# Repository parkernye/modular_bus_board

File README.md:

# modular_bus_board
Modular Synth Bus Board

A PCB that distributes the 10pin or 16pin standard modular synth power. 
LED's for power indication

Future Modifications: 
- Thicker board, or board stiffener

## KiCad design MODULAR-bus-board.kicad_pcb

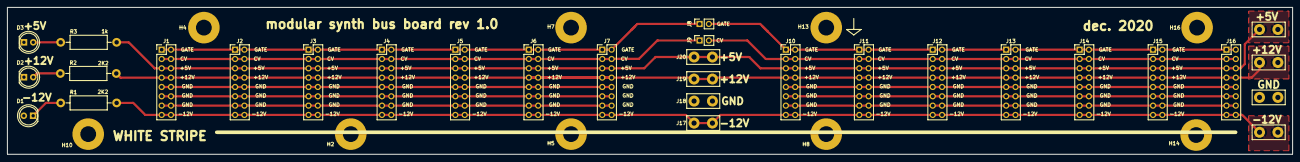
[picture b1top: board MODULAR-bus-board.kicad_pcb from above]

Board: 2 copper layers, 350.0 x 40.0 mm, 39 parts (0 on the bottom side), 11 nets.

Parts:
D1, D2: RED; LED_D5.0mm
D3: YELLOW; LED_D5.0mm
H2, H4, H5, H7, H8, H10, H13, H14, H16: MountingHole_Pad; MountingHole_4.3mm_M4_Pad
J1, J2, J3, J4, J5, J6, J7, J10, J11, J12, J13, J14, J15, J16: Conn_02x08_Odd_Even; PinHeader_2x08_P2.54mm_Vertical
J8, J9: Conn_01x02; PinSocket_1x02_P2.54mm_Vertical
J17, J18, J19, J20, J21: -12V; PCB WELDING TERMINAL TAB PC250
J22: GND; PCB WELDING TERMINAL TAB PC250
J23: +12V; PCB WELDING TERMINAL TAB PC250
J24: +5V; PCB WELDING TERMINAL TAB PC250
R1, R2: 2K2; R_Axial_DIN0411_L9.9mm_D3.6mm_P15.24mm_Horizontal
R3: 1K; R_Axial_DIN0411_L9.9mm_D3.6mm_P15.24mm_Horizontal

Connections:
GND: D1.2, D2.1, D3.1, H2.1, H4.1, H5.1, H7.1, H8.1, H10.1, H13.1, H14.1, H16.1, J1.9, J1.10, J1.11, J1.12, J1.13, J1.14, J2.9, J2.10, J2.11, J2.12, J2.13, J2.14, J3.9, J3.10, J3.11, J3.12, J3.13, J3.14, J4.9, J4.10, J4.11, J4.12, J4.13, J4.14, J5.9, J5.10, J5.11, J5.12, J5.13, J5.14, J6.9, J6.10, J6.11, J6.12, J6.13, J6.14, J7.9, J7.10, J7.11, J7.12, J7.13, J7.14, J10.9, J10.10, J10.11, J10.12, J10.13, J10.14, J11.9, J11.10, J11.11, J11.12, J11.13, J11.14, J12.9, J12.10, J12.11, J12.12, J12.13, J12.14, J13.9, J13.10, J13.11, J13.12, J13.13, J13.14, J14.9, J14.10, J14.11, J14.12, J14.13, J14.14, J15.9, J15.10, J15.11, J15.12, J15.13, J15.14, J16.9, J16.10, J16.11, J16.12, J16.13, J16.14, J20.1, J20.2, J22.1, J22.2
unnamed: D1.1, R1.1
unnamed: D2.2, R2.1
unnamed: D3.2, R3.1
unnamed: J1.1, J1.2, J2.1, J2.2, J3.1, J3.2, J4.1, J4.2, J5.1, J5.2, J6.1, J6.2, J7.1, J7.2, J8.1
unnamed: J1.3, J1.4, J2.3, J2.4, J3.3, J3.4, J4.3, J4.4, J5.3, J5.4, J6.3, J6.4, J7.3, J7.4, J9.1
unnamed: J1.5, J1.6, J2.5, J2.6, J3.5, J3.6, J4.5, J4.6, J5.5, J5.6, J6.5, J6.6, J7.5, J7.6, J10.5, J10.6, J11.5, J11.6, J12.5, J12.6, J13.5, J13.6, J14.5, J14.6, J15.5, J15.6, J16.5, J16.6, J19.1, J19.2, J24.1, J24.2, R3.2
unnamed: J1.7, J1.8, J2.7, J2.8, J3.7, J3.8, J4.7, J4.8, J5.7, J5.8, J6.7, J6.8, J7.7, J7.8, J10.7, J10.8, J11.7, J11.8, J12.7, J12.8, J13.7, J13.8, J14.7, J14.8, J15.7, J15.8, J16.7, J16.8, J18.1, J18.2, J23.1, J23.2, R2.2
unnamed: J1.15, J1.16, J2.15, J2.16, J3.15, J3.16, J4.15, J4.16, J5.15, J5.16, J6.15, J6.16, J7.15, J7.16, J10.15, J10.16, J11.15, J11.16, J12.15, J12.16, J13.15, J13.16, J14.15, J14.16, J15.15, J15.16, J16.15, J16.16, J17.1, J17.2, J21.1, J21.2, R1.2
unnamed: J8.2, J10.1, J10.2, J11.1, J11.2, J12.1, J12.2, J13.1, J13.2, J14.1, J14.2, J15.1, J15.2, J16.1, J16.2
unnamed: J9.2, J10.3, J10.4, J11.3, J11.4, J12.3, J12.4, J13.3, J13.4, J14.3, J14.4, J15.3, J15.4, J16.3, J16.4

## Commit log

2023-11-01 kicadfiles
